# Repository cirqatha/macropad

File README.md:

# DESKPAD

A 3-key macropad with rotary encoder, OLED display, and RGB underglow for volume display, all coded in QMK.

## Overall Hackpad

## Schematic

## PCB

## Case

## BOM
| Component | Part | Quantity |
|---|---|---|
| Diodes | 1N4148 | 4 |
| RGB LEDs | SK6812MINI | 6 |
| Display | OLED 128x32 | 1 |
| Switches | MX Push Switch | 3 |
| Encoder | Rotary Encoder | 1 |
| MCU | Seeed XIAO RP2040 | 1 |

## Firmware
Built with QMK. Features:
- Desktop switching shortcuts
- Volume control via encoder
- RGB volume indicator
- OLED display

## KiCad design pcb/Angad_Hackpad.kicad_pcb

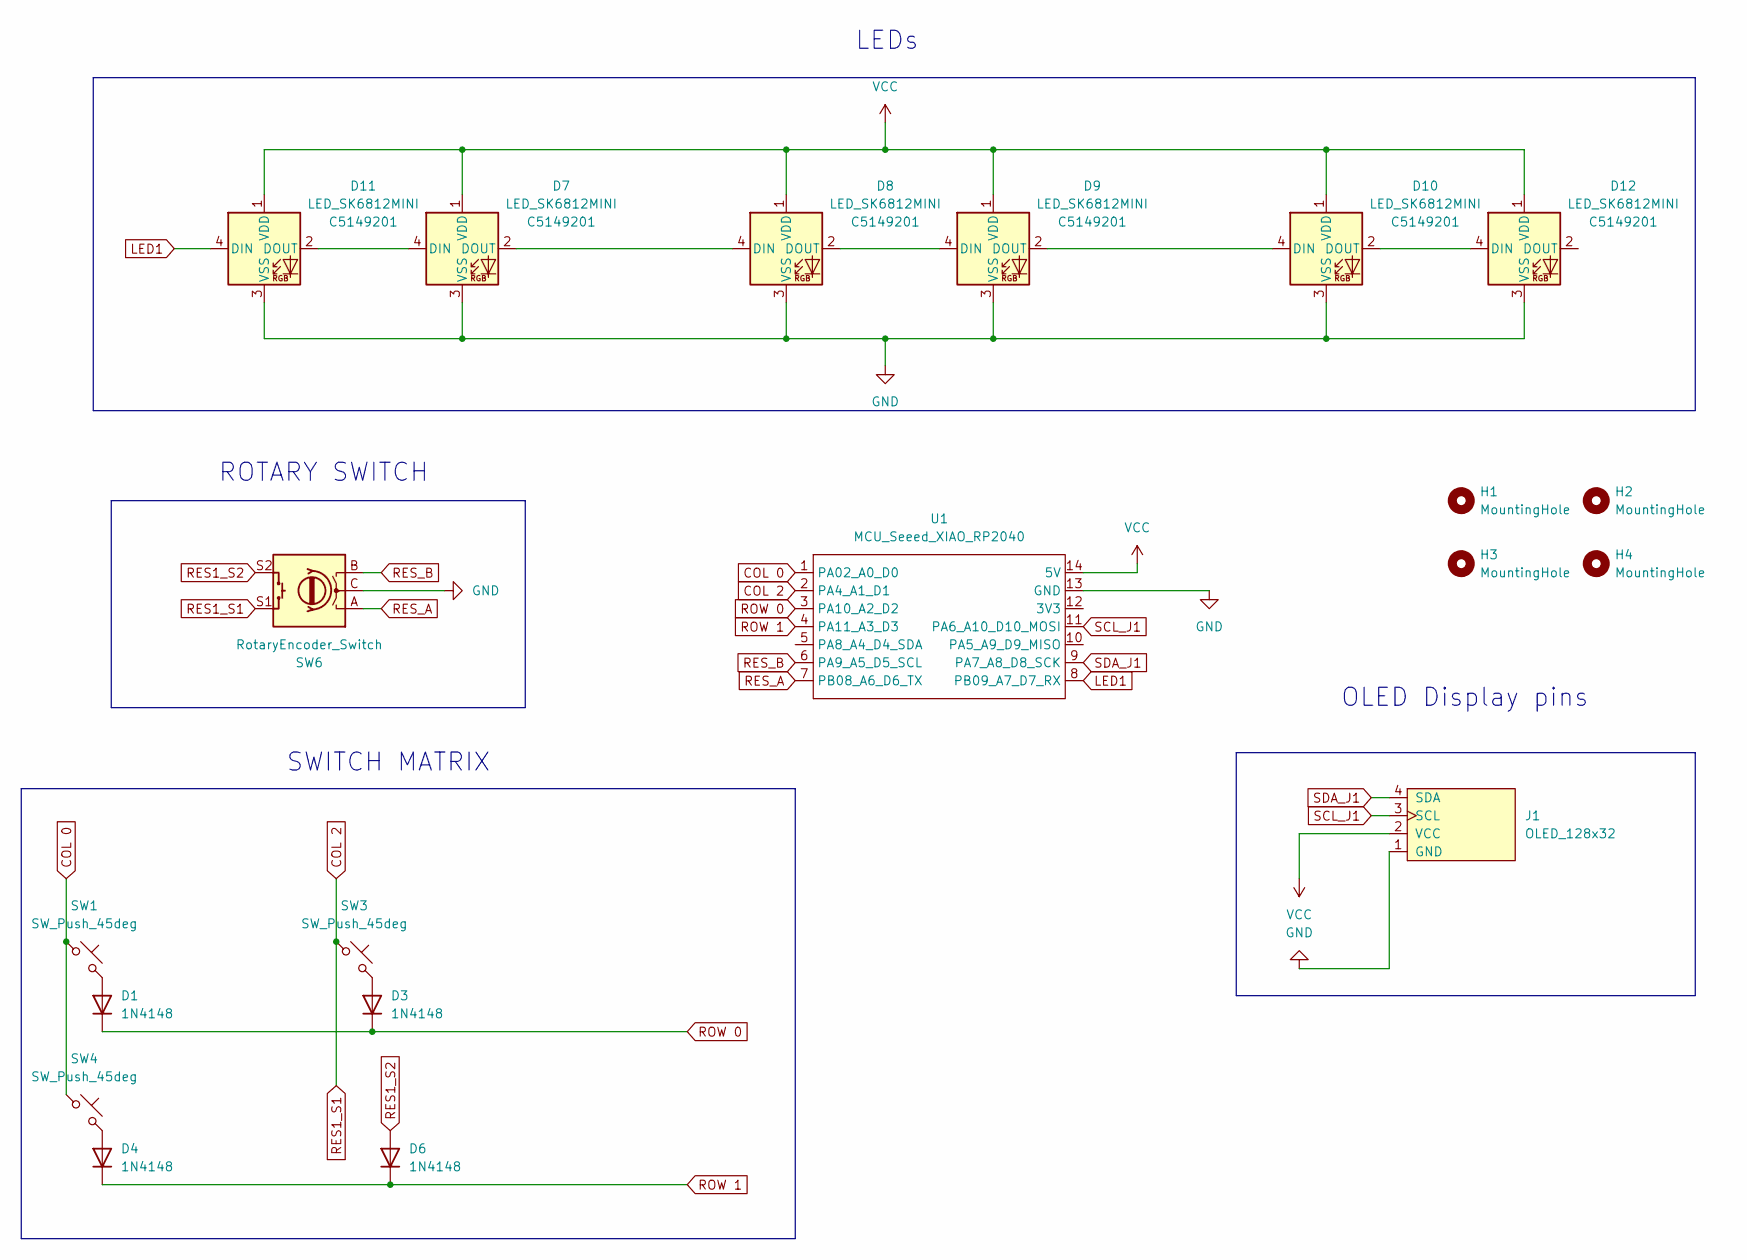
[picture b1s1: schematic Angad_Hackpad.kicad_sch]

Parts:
D1, D3, D4, D6: 1N4148; D_DO-35_SOD27_P7.62mm_Horizontal
D7, D8, D9, D10, D11, D12: LED_SK6812MINI; LCSC C5149201
H1, H2, H3, H4: MountingHole; MountingHole_3.2mm_M3
J1: OLED_128x32
SW1, SW3, SW4: SW_Push_45deg; MX_PCB_1.00u
SW6: RotaryEncoder_Switch; Encoder_EC11_MX
U1: MCU_Seeed_XIAO_RP2040; Seeed_XIAO_RP2040

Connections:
COL 0: SW1.1, SW4.1, U1.1 (PA02_A0_D0)
COL 2: SW3.1, SW6.S1, U1.2 (PA4_A1_D1)
GND: D7.3 (VSS), D8.3 (VSS), D9.3 (VSS), D10.3 (VSS), D11.3 (VSS), D12.3 (VSS), J1.1 (GND), SW6.C, U1.13 (GND)
LED1: D11.4 (DIN), U1.8 (PB09_A7_D7_RX)
unnamed: D1.2 (A), SW1.2
unnamed: D3.2 (A), SW3.2
unnamed: D4.2 (A), SW4.2
unnamed: D7.2 (DOUT), D8.4 (DIN)
unnamed: D8.2 (DOUT), D9.4 (DIN)
unnamed: D9.2 (DOUT), D10.4 (DIN)
unnamed: D10.2 (DOUT), D12.4 (DIN)
unnamed: D7.4 (DIN), D11.2 (DOUT)
RES1_S2: D6.2 (A), SW6.S2
RES_A: SW6.A, U1.7 (PB08_A6_D6_TX)
RES_B: SW6.B, U1.6 (PA9_A5_D5_SCL)
ROW 0: D1.1 (K), D3.1 (K), U1.3 (PA10_A2_D2)
ROW 1: D4.1 (K), D6.1 (K), U1.4 (PA11_A3_D3)
SCL_J1: J1.3 (SCL), U1.11 (PA6_A10_D10_MOSI)
SDA_J1: J1.4 (SDA), U1.9 (PA7_A8_D8_SCK)
VCC: D7.1 (VDD), D8.1 (VDD), D9.1 (VDD), D10.1 (VDD), D11.1 (VDD), D12.1 (VDD), J1.2 (VCC), U1.14 (5V)

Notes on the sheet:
ROTARY SWITCH
OLED Display pins
LEDs
SWITCH MATRIX

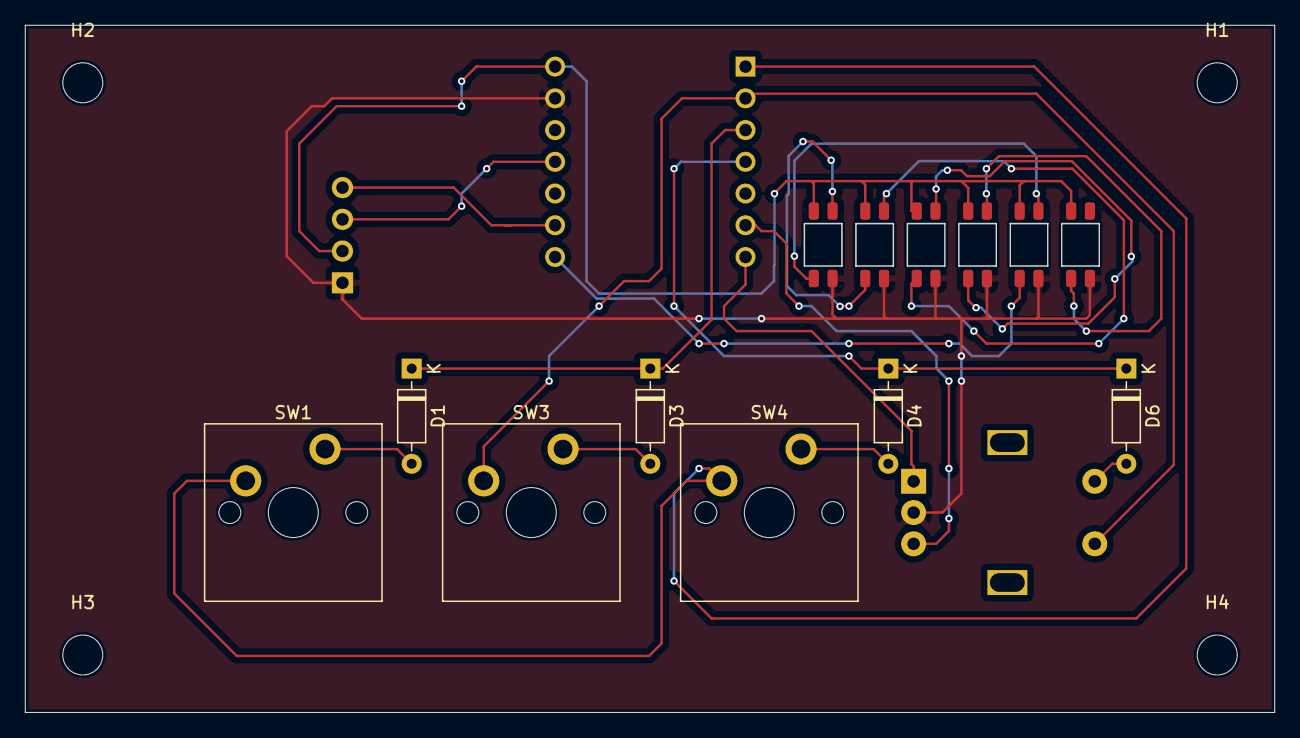
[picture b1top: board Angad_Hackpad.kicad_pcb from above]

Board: 2 copper layers, 100.0 x 55.0 mm, 20 parts (1 on the bottom side), 20 nets.
